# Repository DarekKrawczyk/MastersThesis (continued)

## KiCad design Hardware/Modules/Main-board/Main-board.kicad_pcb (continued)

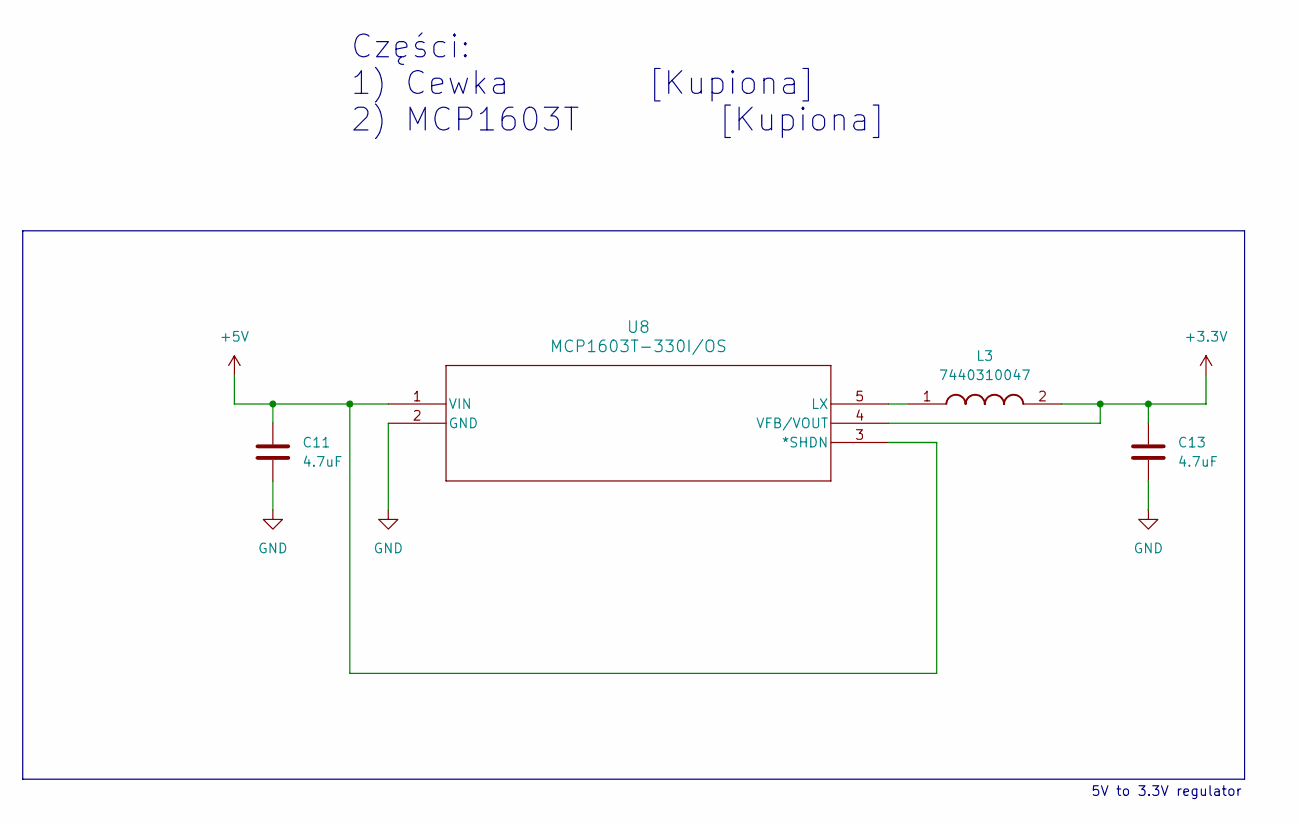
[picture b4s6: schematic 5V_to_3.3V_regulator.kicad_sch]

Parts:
C11, C13: 4.7uF; C_1206_3216Metric
L3: 7440310047; WE-TPC_381692; Mouser Part Number 710-7440310047
U8: MCP1603T-330I/OS; TSOT5_MC_MCH

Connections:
unnamed: L3.1, U8.5 (LX)

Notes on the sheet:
5V to 3.3V regulator
Części: 1) Cewka [Kupiona] 2) MCP1603T [Kupiona]

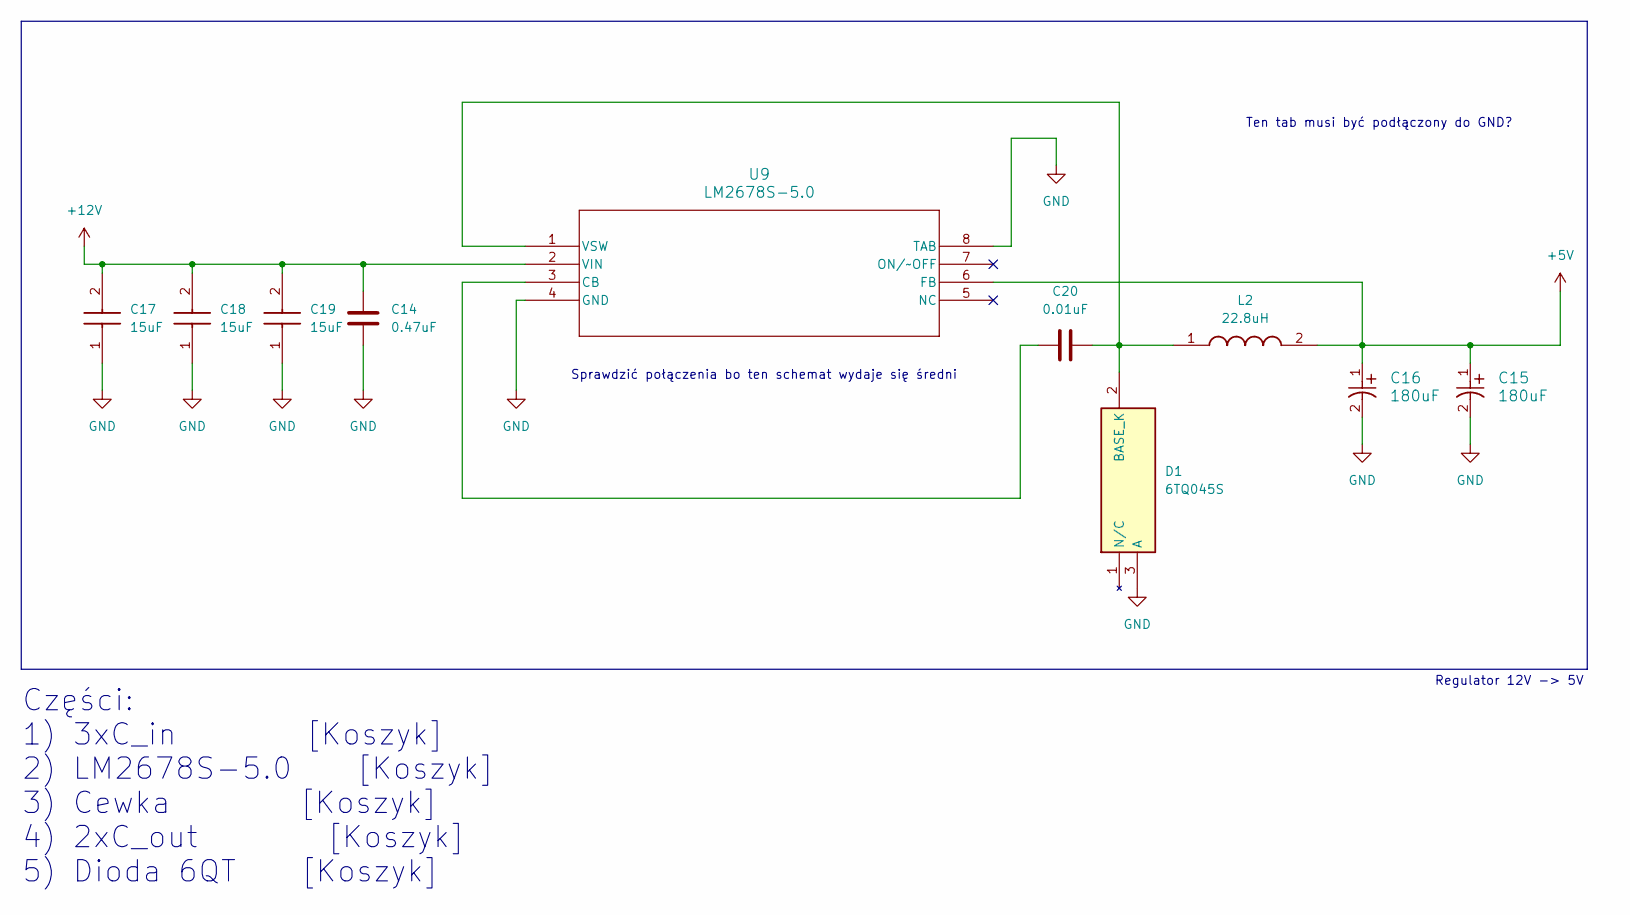
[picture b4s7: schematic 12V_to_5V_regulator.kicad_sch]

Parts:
C14: 0.47uF; C_1206_3216Metric
C15, C16: 180uF; PCAP_SVP_F8_PAN
C17, C18, C19: 15uF; CAPCP6032X280N; Mouser Part Number 581-TPSC156K035R0350
C20: 0.01uF; C_1206_3216Metric
D1: 6TQ045S; Mouser Part Number 844-6TQ045S
L2: 22.8uH; P0841NL; Mouser Part Number 673-P0841NL
U9: LM2678S-5.0; TS7B

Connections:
+12V: C14.1, C17.2 (C2), C18.2 (C2), C19.2 (C2), U9.2 (VIN); also elsewhere on the board
unnamed: C20.1, D1.2 (BASE_K), L2.1, U9.1 (VSW)
unnamed: C20.2, U9.3 (CB)

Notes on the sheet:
Regulator 12V -> 5V
Części: 1) 3xC_in [Koszyk] 2) LM2678S-5.0 [Koszyk] 3) Cewka [Koszyk] 4) 2xC_out [Koszyk] 5) Dioda 6QT [Koszyk]
Ten tab musi być podłączony do GND?
Sprawdzić połączenia bo ten schemat wydaje się średni

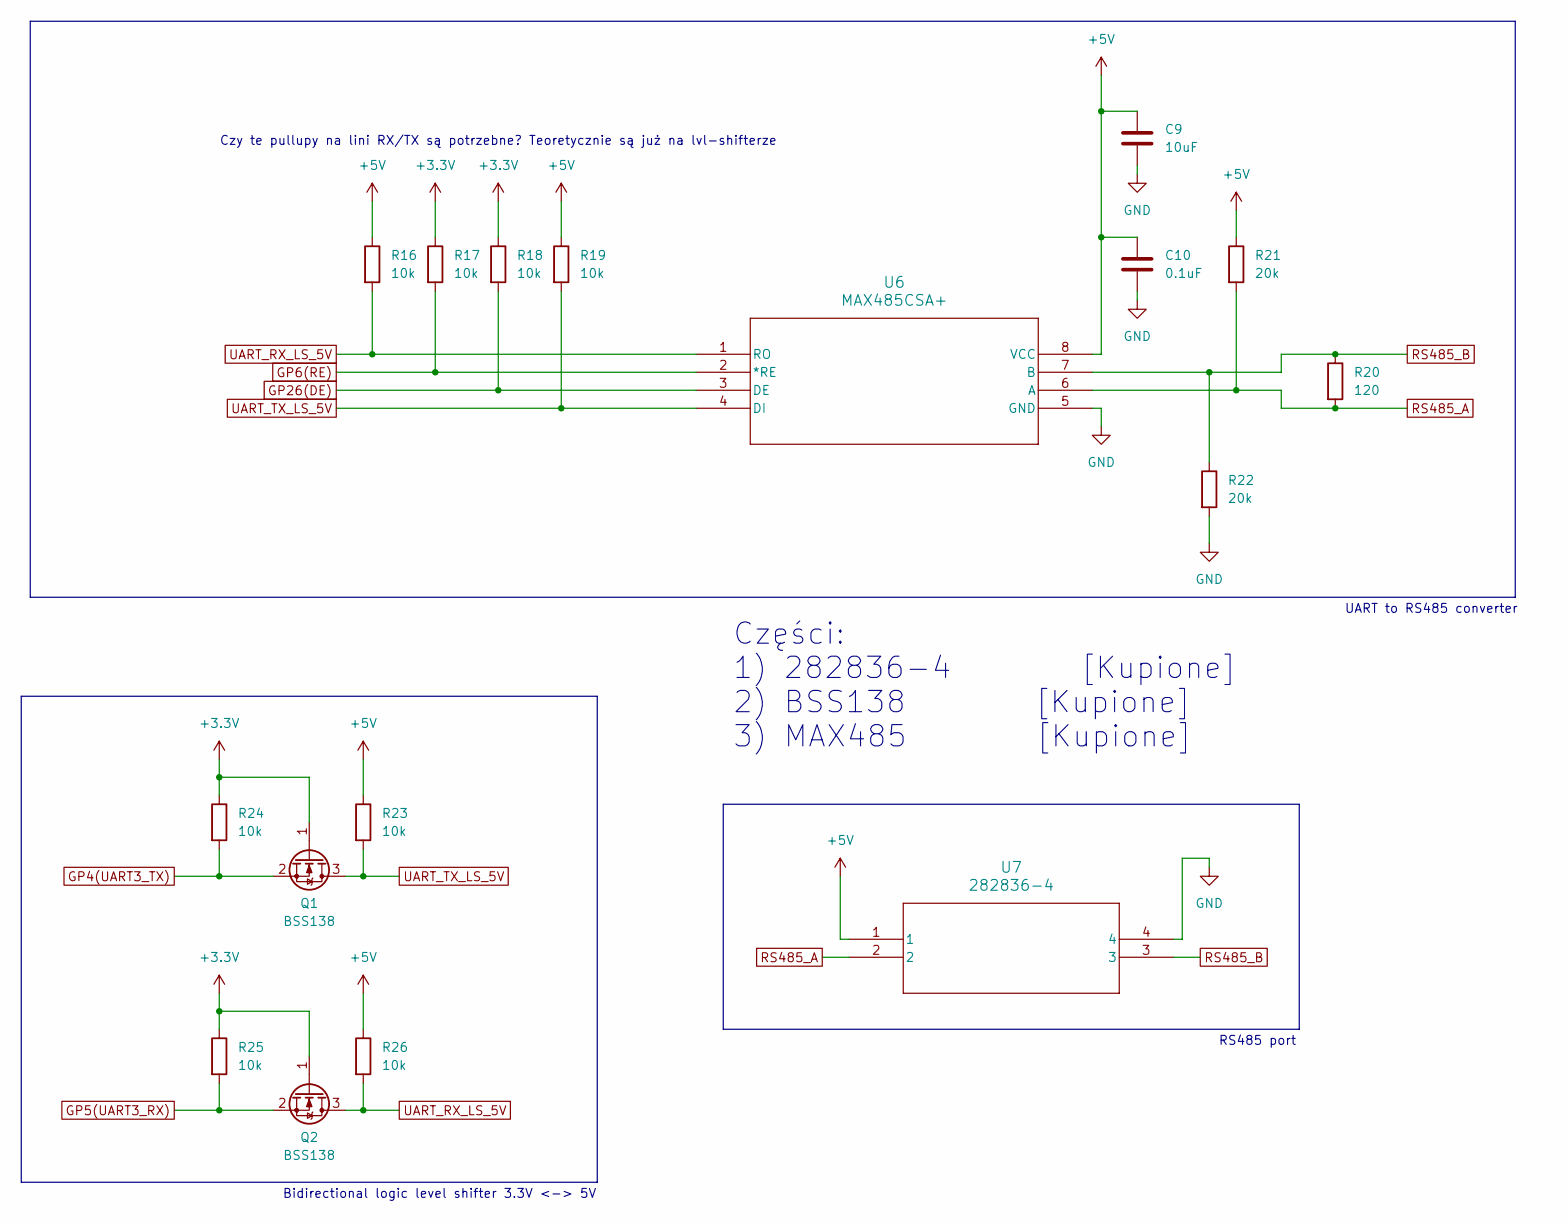
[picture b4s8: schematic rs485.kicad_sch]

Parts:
C9: 10uF; C_1206_3216Metric
C10: 0.1uF; C_1206_3216Metric
Q1, Q2: BSS138; SOT-23
R16, R17, R18, R19, R23, R24, R25, R26: 10k; R_1206_3216Metric
R20: 120; R_1206_3216Metric
R21, R22: 20k; R_1206_3216Metric
U6: MAX485CSA+; 21-0041B_8_MXM
U7: 282836-4; 282836-4_TYC

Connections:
GP4(UART3_TX): Q1.2 (S), R24.2; also elsewhere on the board
GP5(UART3_RX): Q2.2 (S), R25.2; also elsewhere on the board
GP6(RE): R17.2, U6.2 (*RE); also elsewhere on the board
GP26(DE): R18.2, U6.3 (DE); also elsewhere on the board
RS485_A: R20.2, R21.2, U6.6 (A), U7.2
RS485_B: R20.1, R22.1, U6.7 (B), U7.3
UART_RX_LS_5V: Q2.3 (D), R16.2, R26.2, U6.1 (RO)
UART_TX_LS_5V: Q1.3 (D), R19.2, R23.2, U6.4 (DI)

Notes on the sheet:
RS485 port
Części: 1) 282836-4 [Kupione] 2) BSS138 [Kupione] 3) MAX485 [Kupione]
Czy te pullupy na lini RX/TX są potrzebne? Teoretycznie są już na lvl-shifterze
Bidirectional logic level shifter 3.3V <-> 5V
UART to RS485 converter

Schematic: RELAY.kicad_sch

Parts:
CR1, CR2: S1MTR; SMA_SDS
J8, J28: 1546551-3; CONN3_1546551-3_TEC
K1, K2: G5LE-14 DC5; RELAY_G5LE-1 DC5_OMR
LED1, LED2: LTST-C150GKT; LED_LTST-C150GKT_LTO
R13, R15, R27, R28: 510; R_1206_3216Metric
R14, R29: 470; R_1206_3216Metric
TR1, TR2: MMBT2222A-TP; MTR_MMBT2222A-TP_MCE
U5, U10: WL-OCP_DIP4_SLM-TYPE; WL-OCPT_DIP4_SLM-TYPE

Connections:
GP24(RELAY_0): R15.1; also elsewhere on the board
GP25(RELAY_1): R27.1; also elsewhere on the board
unnamed: CR1.2, K1.2, LED1.1, TR1.3
unnamed: CR2.2, K2.2, LED2.1, TR2.3
unnamed: J8.1, K1.4
unnamed: J8.2, K1.1
unnamed: J8.3, K1.3
unnamed: J28.1, K2.4
unnamed: J28.2, K2.1
unnamed: J28.3, K2.3
unnamed: LED1.2, R14.2
unnamed: LED2.2, R29.2
unnamed: R13.1, U5.3
unnamed: R13.2, TR1.1
unnamed: R15.2, U5.1
unnamed: R27.2, U10.1
unnamed: R28.1, U10.3
unnamed: R28.2, TR2.1

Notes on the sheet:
Części: 1) 2xPrzekaźnik [Kupione ostatnio] 2) 2xS1MTR [Kupione ostatnio] 3) 2xOpto [Kupione ostatnio] 4) 2xTranzystor [Kupione ostatnio] 5) 2xLED [Kupione] 6) 2xPowerPin [Kupione]

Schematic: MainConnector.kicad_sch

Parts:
J4, J11, J13, J14, J15, J18, J20: Conn_01x08; PinHeader_1x08_P2.54mm_Vertical
J9: Conn_02x20_Odd_Even; PinHeader_2x20_P2.54mm_Vertical
J10, J12, J19: Conn_02x08_Odd_Even; PinHeader_2x08_P2.54mm_Vertical
J16, J17: Conn_01x20; PinHeader_1x20_P2.54mm_Vertical
J29, J37: Conn_02x04_Odd_Even; PinSocket_2x04_P2.54mm_Vertical
J30, J31, J32, J34: Conn_01x04; PinHeader_1x04_P2.54mm_Vertical

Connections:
GP0(DONTUSE): J9.27, J16.7
GP1(DONTUSE): J9.28, J17.14
GP2(I2C1_SDA): J9.3, J12.1, J12.3, J12.5, J12.7, J12.9, J12.11, J12.13, J12.15, J16.19; also elsewhere on the board
GP3(I2C1_SCL): J9.5, J12.2, J12.4, J12.6, J12.8, J12.10, J12.12, J12.14, J12.16, J16.18; also elsewhere on the board
GP4(UART3_TX): J9.7, J16.17, J37.2, J37.4, J37.6, J37.8; also elsewhere on the board
GP5(UART3_RX): J9.29, J16.6, J37.1, J37.3, J37.5, J37.7; also elsewhere on the board
GP6(RE): J9.31, J16.5; also elsewhere on the board
GP7(UNUSED): J9.26, J17.13
GP8(SPI0_CS): J9.24, J17.12; also elsewhere on the board
GP9(SPI0_MISO): J9.21, J16.10; also elsewhere on the board
GP10(SPI0_MOSI): J9.19, J16.11; also elsewhere on the board
GP11(SPI0_CLK): J9.23, J16.9; also elsewhere on the board
GP12(I2C5_SDA/UART5_TX): J9.32, J17.16, J19.1, J19.3, J19.5, J19.7, J19.9, J19.11, J19.13, J19.15
GP13(I2C5_SCL/UART5_RX): J9.33, J16.4, J19.2, J19.4, J19.6, J19.8, J19.10, J19.12, J19.14, J19.16
GP14(UART0_TX): J9.8, J17.4, J29.2, J29.4, J29.6, J29.8
GP15(UART0_RX): J9.10, J17.5, J29.1, J29.3, J29.5, J29.7
GP16(UNUSED): J9.36, J17.18
GP17(UNUSED): J9.11, J16.15
GP18(SPI1_CS): J9.12, J17.6
GP19(SPI1_MISO): J9.35, J16.3
GP20(SPI1_MOSI): J9.38, J17.19
GP21(SPI1_CLK): J9.40, J17.20
GP22(I2C6_SDA): J9.15, J10.1, J10.3, J10.5, J10.7, J10.9, J10.11, J10.13, J10.15, J16.13
GP23(I2C6_SCL): J9.16, J10.2, J10.4, J10.6, J10.8, J10.10, J10.12, J10.14, J10.16, J17.8
GP24(RELAY_0): J9.18, J17.9; also elsewhere on the board
GP25(RELAY_1): J9.22, J17.11; also elsewhere on the board
GP26(DE): J9.37, J16.2; also elsewhere on the board
GP27(UNUSED): J9.13, J16.14
unnamed: J9.17, J16.12
unnamed: J9.1, J16.20

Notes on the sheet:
UART0 pins
I2C6/UART5 pins
Części: 1) 4xConn01x20 [Kupione] 2) 12xConn01x08 [Kupione] 3) 8xConn01x04 [Kupione] 4) Conn do RPi [Kupione] 5) Taśma [Nie kupiona]
UART3 pins
I2C6 pins
Power pins
Main connector
I2C1 pins
Podłączenie RPi do zasilania

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
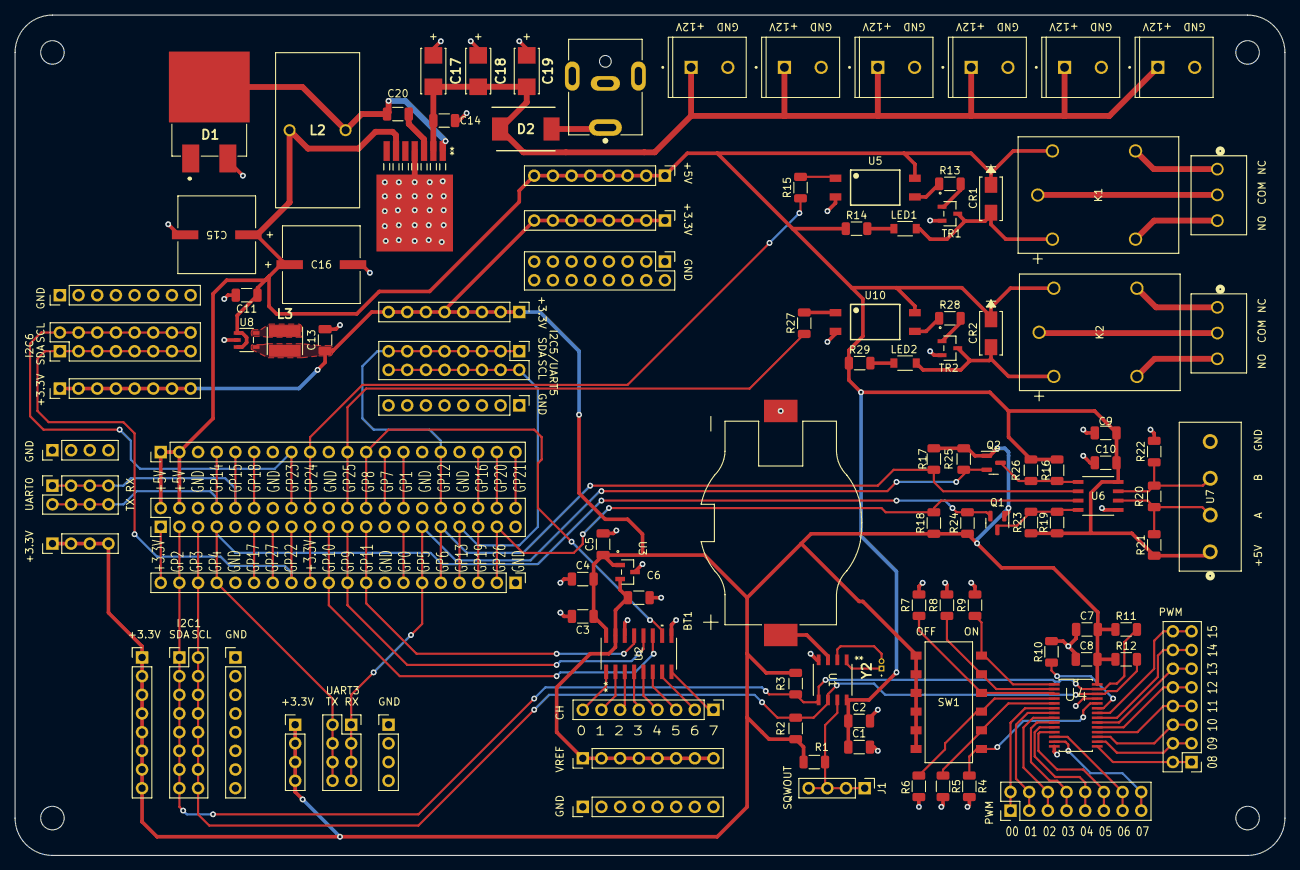
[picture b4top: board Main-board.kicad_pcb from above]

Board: 2 copper layers, 172.7 x 114.3 mm, 115 parts (0 on the bottom side), 94 nets.

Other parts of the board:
J5, J36: Conn_01x08; PinHeader_1x08_P2.54mm_Vertical

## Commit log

2026-03-13 Readme update
